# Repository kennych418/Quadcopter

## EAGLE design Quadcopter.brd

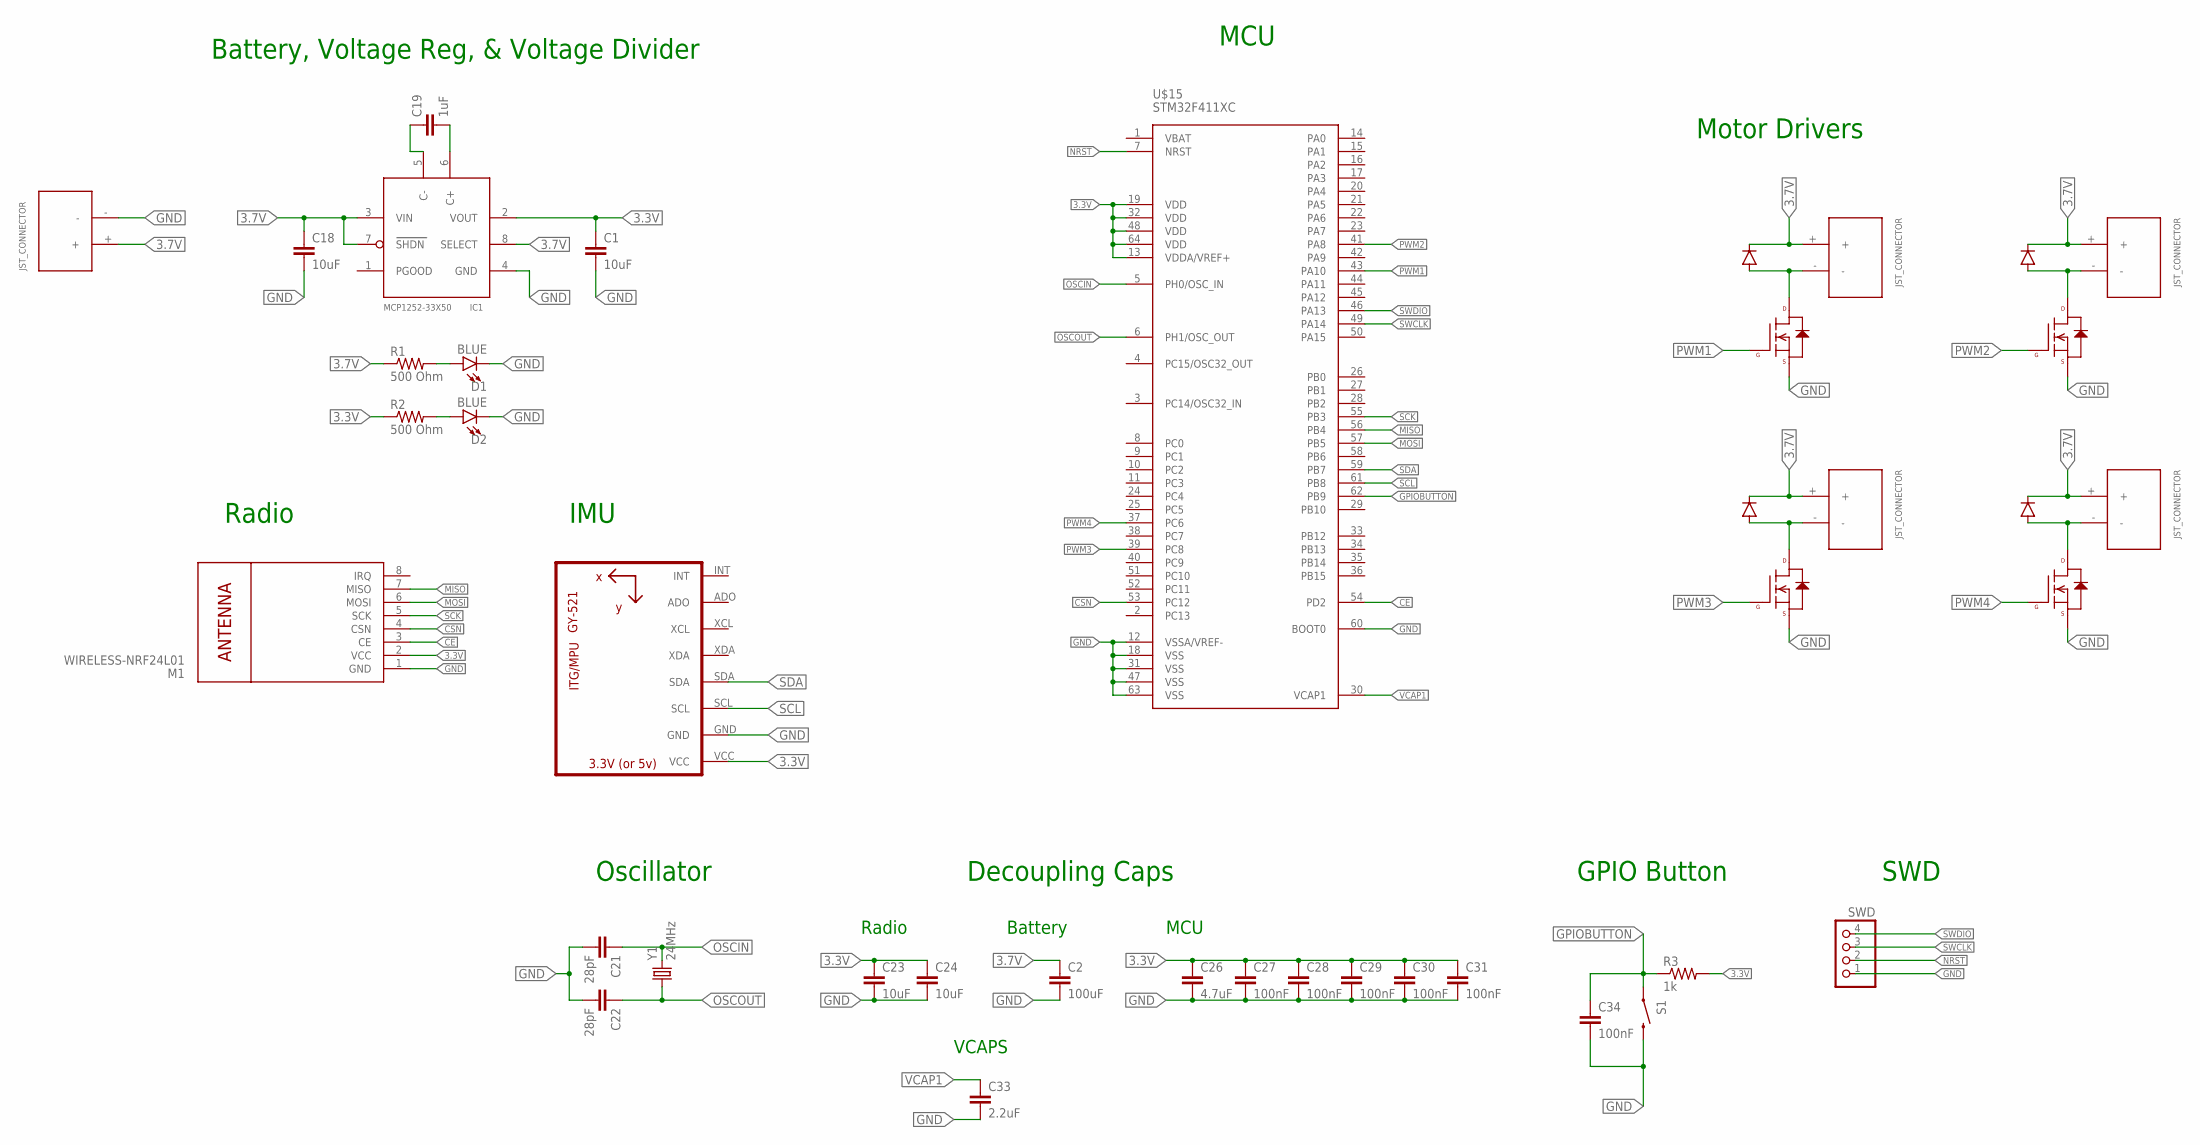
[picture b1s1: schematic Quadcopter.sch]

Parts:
C1, C18, C23, C24: 10uF; C0402K
C2: 100uF; C1206
C19: 1uF; C0402K
C21, C22: 28pF; C0402K
C26: 4.7uF; C0402K
C27, C28, C29, C30, C31, C34: 100nF; C0402K
C33: 2.2uF; C0402K
D1, D2: BLUE; LED-0603
IC1: MCP1252-33X50; MSOP8
JP1: SWD; 1X04
M1: WIRELESS-NRF24L01
R1, R2: 500 Ohm; R0402
R3: 1k; R0402
S1: SWITCH-MOMENTARY-2SMD; TACTILE-SWITCH-SMD
U1: GY-521MPU6050; GY-521
U$2, U$3, U$4, U$7, U$11: JST_CONNECTOR_FEMALE
U$5, U$8, U$10, U$12: N-CHANNEL-MOSFET-IRLML6244TRPBF; SOT23-3
U$6, U$9, U$13, U$14: DB2W40300L; MINI2-F3-B
U$15: STM32F411XC; LQFP64
Y1: 24MHz; HC49UP

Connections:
3.3V: C1.1, C23.1, C24.1, C26.1, C27.1, C28.1, C29.1, C30.1, C31.1, IC1.2 (VOUT), M1.2 (VCC), R2.1, R3.2, U1.VCC, U$15.13 (VDDA/VREF+), U$15.19 (VDD), U$15.32 (VDD), U$15.48 (VDD), U$15.64 (VDD)
3.7V: C2.1, C18.1, IC1.3 (VIN), IC1.7 (SHDN), IC1.8 (SELECT), R1.1, U$2.+, U$3.+, U$4.+, U$6.NEG (GPIN), U$7.+, U$9.NEG (GPIN), U$11.+, U$13.NEG (GPIN), U$14.NEG (GPIN)
CE: M1.3 (CE), U$15.54 (PD2)
CSN: M1.4 (CSN), U$15.53 (PC12)
GND: C1.2, C2.2, C18.2, C21.2, C22.2, C23.2, C24.2, C26.2, C27.2, C28.2, C29.2, C30.2, C31.2, C33.2, C34.2, D1.C, D2.C, IC1.4 (GND), JP1.1, M1.1 (GND), S1.3 (2), U1.GND, U$3.-, U$5.2 (S), U$8.2 (S), U$10.2 (S), U$12.2 (S), U$15.12 (VSSA/VREF-), U$15.18 (VSS), U$15.31 (VSS), U$15.47 (VSS), U$15.60 (BOOT0), U$15.63 (VSS)
GPIOBUTTON: C34.1, R3.1, S1.1, U$15.62 (PB9)
MISO: M1.7 (MISO), U$15.56 (PB4)
MOSI: M1.6 (MOSI), U$15.57 (PB5)
unnamed: U$4.-, U$10.3 (D), U$14.POS (PPIN)
unnamed: U$2.-, U$5.3 (D), U$6.POS (PPIN)
unnamed: U$7.-, U$8.3 (D), U$9.POS (PPIN)
unnamed: U$11.-, U$12.3 (D), U$13.POS (PPIN)
unnamed: C19.1, IC1.5 (C-)
unnamed: C19.2, IC1.6 (C+)
unnamed: D1.A, R1.2
unnamed: D2.A, R2.2
NRST: JP1.2, U$15.7 (NRST)
OSCIN: C21.1, U$15.5 (PH0/OSC_IN), Y1.2
OSCOUT: C22.1, U$15.6 (PH1/OSC_OUT), Y1.1
PWM1: U$10.1 (G), U$15.43 (PA10)
PWM2: U$5.1 (G), U$15.41 (PA8)
PWM3: U$8.1 (G), U$15.39 (PC8)
PWM4: U$12.1 (G), U$15.37 (PC6)
SCK: M1.5 (SCK), U$15.55 (PB3)
SCL: U1.SCL, U$15.61 (PB8)
SDA: U1.SDA, U$15.59 (PB7)
SWCLK: JP1.3, U$15.49 (PA14)
SWDIO: JP1.4, U$15.46 (PA13)
VCAP1: C33.1, U$15.30 (VCAP1)

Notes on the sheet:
Oscillator
Motor Drivers
Radio
IMU
Battery, Voltage Reg, & Voltage Divider
MCU
Decoupling Caps
Battery
SWD
GPIO Button
VCAPS

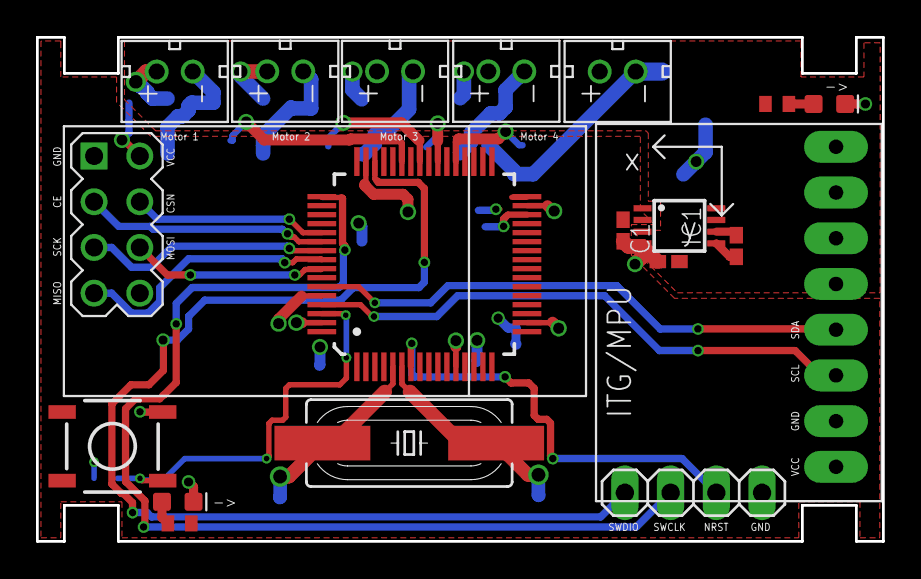
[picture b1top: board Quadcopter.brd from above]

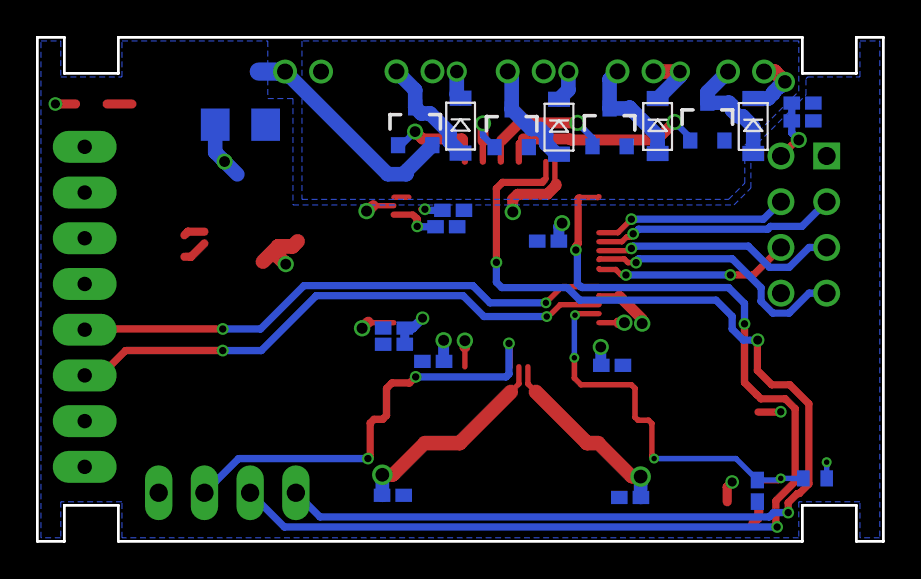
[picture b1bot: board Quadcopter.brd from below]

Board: 2 copper layers, 47.0 x 28.0 mm, 41 parts (22 on the bottom side), 29 nets.

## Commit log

2019-12-12 Adding Eagle and BOM

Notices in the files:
parts and their libraries:
SparkFun-LED: Licensing: Creative Commons ShareAlike 4.0 International - https://creativecommons.org/licenses/by-sa/4.0
